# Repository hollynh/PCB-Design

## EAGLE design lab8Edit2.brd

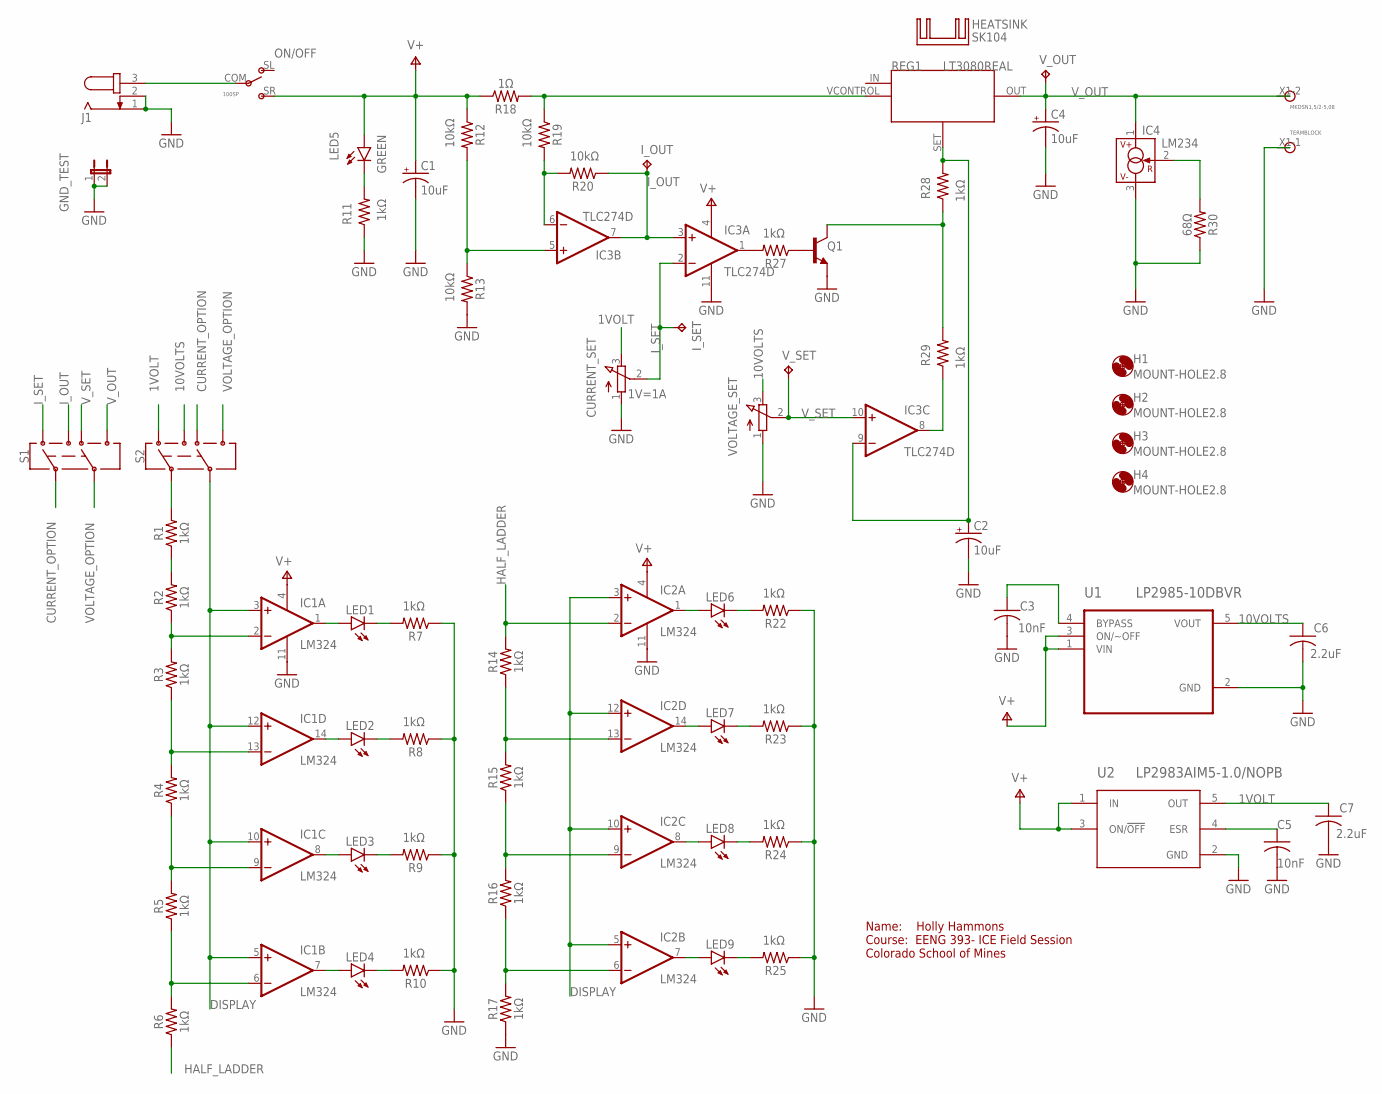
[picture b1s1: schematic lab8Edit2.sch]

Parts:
C1, C2, C4: 10uF; PANASONIC_B
C3, C5: 10nF; C1206
C6, C7: 2.2uF; C1206
CURRENT_SET: 1V=1A; EVUF
GND_TEST: JP1E; JP1
H1, H2, H3, H4: MOUNT-HOLE2.8; 2,8
HEATSINK: SK104
IC1, IC2: LM324; SO14
IC3: TLC274D; SO14
IC4: LM234; TO92
I_OUT: TPPAD1-13; P1-13
I_SET: TPPAD1-13; P1-13
J1: JACK-PLUG0; SPC4077
LED1, LED2, LED3, LED4, LED6, LED7, LED8, LED9: LEDCHIPLED_1206; CHIPLED_1206
LED5: GREEN; CHIPLED_1206
MKDSN1,5/2-5,08: TERMBLOCK
ON/OFF: 100SP; SP100
Q1: TRANS_NPN-MMBTA42; SOT23-3
R1, R2, R3, R4, R5, R6, R7, R8, R9, R10, R11, R14, R15, R16, R17, R22, R23, R24, R25, R27, R28, R29: 1kΩ; R1206
R12, R13, R19, R20: 10kΩ; R1206
R18: 1Ω; 0411/15
R30: 68Ω; R1206
REG1: LT3080REAL
S1, S2: SWITCH-DPDT-SMD-AYZ0202; SWITCH_DPDT_SMD_AYZ0202
U1: LP2985-10DBVR; SOT95P280X145-5N
U2: LP2983AIM5-1.0/NOPB; SOT95P280X145-5N
VOLTAGE_SET: EVUF2A; EVUF
V_OUT: TPPAD1-13; P1-13
V_SET: TPPAD1-13; P1-13

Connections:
1VOLT: C7.1, CURRENT_SET.3 (E), S2.3, U2.5 (OUT)
10VOLTS: C6.1, S2.1, U1.5 (VOUT), VOLTAGE_SET.3 (E)
CURRENT_OPTION: S1.2, S2.6
DISPLAY: IC1.3 (+IN), IC1.5 (+IN), IC1.10 (+IN), IC1.12 (+IN), IC2.3 (+IN), IC2.5 (+IN), IC2.10 (+IN), IC2.12 (+IN), S2.5
GND: C1.-, C2.-, C3.2, C4.-, C5.2, C6.2, C7.2, CURRENT_SET.1 (A), GND_TEST.1, GND_TEST.2, IC1.11 (V-), IC2.11 (V-), IC3.11 (V-), IC4.3 (V-), J1.1, J1.2, MKDSN1,5/2-5,08.X1-1, Q1.2 (E), R7.1, R8.1, R9.1, R10.1, R11.1, R13.2, R17.1, R22.1, R23.1, R24.1, R25.1, R30.1, U1.2 (GND), U2.2 (GND), VOLTAGE_SET.1 (A)
HALF_LADDER: IC2.2 (-IN), R6.1, R14.2
I_OUT: IC3.3 (+IN), IC3.7 (OUT), I_OUT.TP, R20.1, S1.1
I_SET: CURRENT_SET.2 (S), IC3.2 (-IN), I_SET.TP, S1.3
unnamed: J1.3, ON/OFF.COM
unnamed: LED5.C, R11.2
unnamed: C2.+, IC3.9 (-IN), R28.2, REG1.SET
unnamed: R1.2, S2.2
unnamed: IC3.8 (OUT), R29.1
unnamed: Q1.3 (C), R28.1, R29.2
unnamed: Q1.1 (B), R27.1
unnamed: IC3.5 (+IN), R12.2, R13.1
unnamed: IC4.2 (R), R30.2
unnamed: R18.2, R19.1, REG1.VCONTROL (VCTL)
unnamed: IC3.6 (-IN), R19.2, R20.2
unnamed: IC3.1 (OUT), R27.2
unnamed: LED2.C, R8.2
unnamed: IC1.6 (-IN), R5.1, R6.2
unnamed: IC1.9 (-IN), R4.1, R5.2
unnamed: IC1.13 (-IN), R3.1, R4.2
unnamed: IC1.2 (-IN), R2.1, R3.2
unnamed: R1.1, R2.2
unnamed: C3.1, U1.4 (BYPASS)
unnamed: IC1.7 (OUT), LED4.A
unnamed: LED4.C, R10.2
unnamed: IC1.8 (OUT), LED3.A
unnamed: LED3.C, R9.2
unnamed: IC1.14 (OUT), LED2.A
unnamed: IC1.1 (OUT), LED1.A
unnamed: LED1.C, R7.2
unnamed: LED7.C, R23.2
unnamed: IC2.6 (-IN), R16.1, R17.2
unnamed: IC2.9 (-IN), R15.1, R16.2
unnamed: IC2.13 (-IN), R14.1, R15.2
unnamed: C5.1, U2.4 (ESR)
unnamed: IC2.7 (OUT), LED9.A
unnamed: LED9.C, R25.2
unnamed: IC2.8 (OUT), LED8.A
unnamed: LED8.C, R24.2
unnamed: IC2.14 (OUT), LED7.A
unnamed: IC2.1 (OUT), LED6.A
unnamed: LED6.C, R22.2
V+: C1.+, IC1.4 (V+), IC2.4 (V+), IC3.4 (V+), LED5.A, ON/OFF.SR, R12.1, R18.1, U1.1 (VIN), U1.3 (ON/~OFF), U2.1 (IN), U2.3 (ON/!OFF)
VOLTAGE_OPTION: S1.5, S2.4
V_OUT: C4.+, IC4.1 (V+), MKDSN1,5/2-5,08.X1-2, REG1.OUT, S1.4, V_OUT.TP
V_SET: IC3.10 (+IN), S1.6, VOLTAGE_SET.2 (S), V_SET.TP

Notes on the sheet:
Name: Holly Hammons Course: EENG 393- ICE Field Session Colorado School of Mines

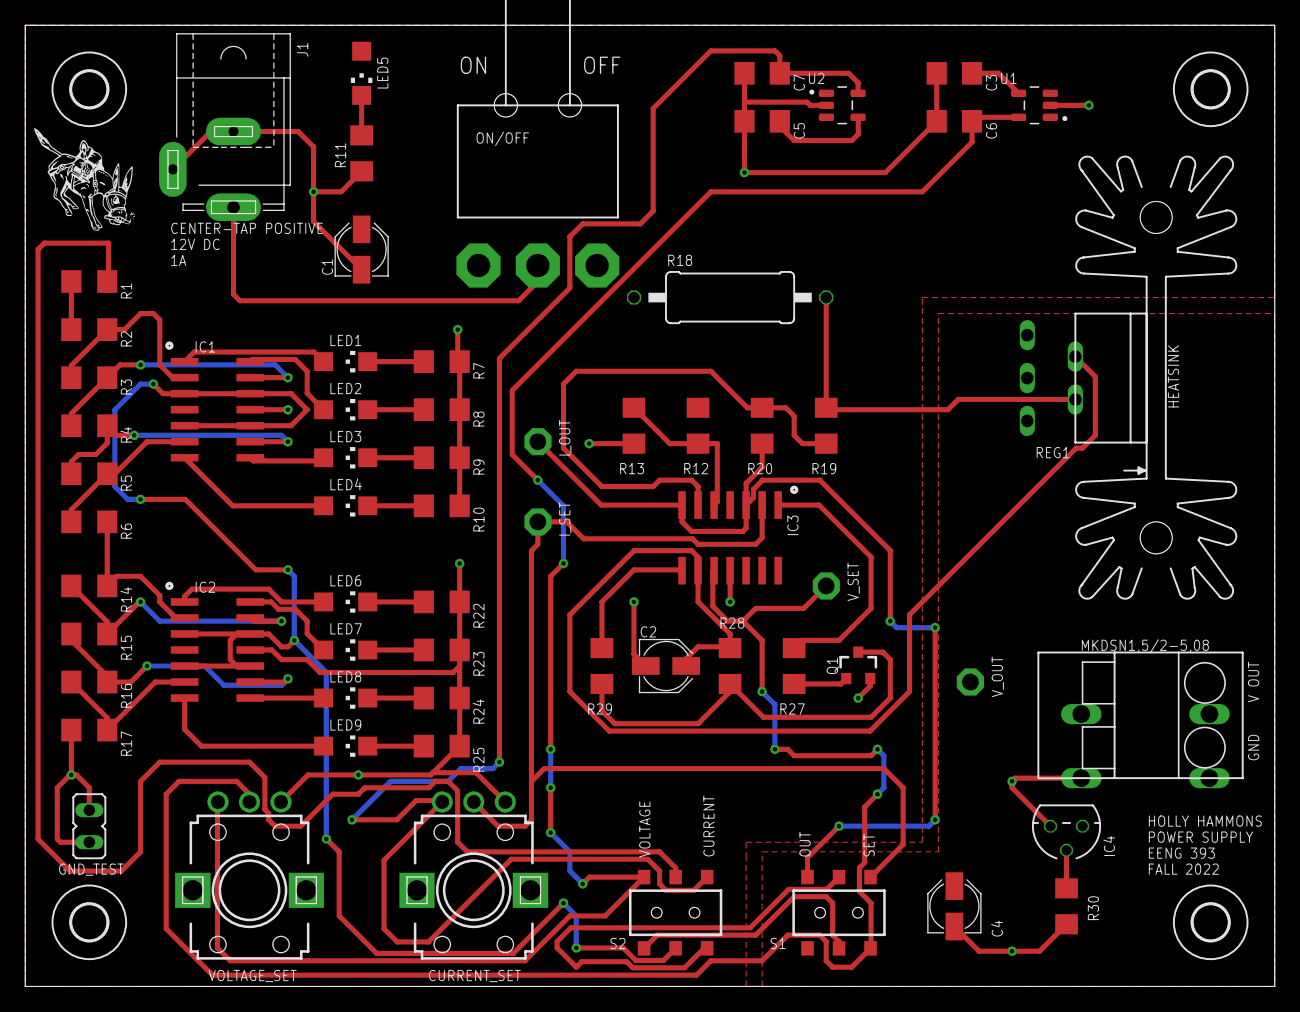
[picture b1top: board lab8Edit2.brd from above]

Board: 2 copper layers, 99.1 x 76.2 mm, 69 parts (0 on the bottom side), 50 nets.

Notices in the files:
parts and their libraries:
SparkFun-DiscreteSemi: Licensing: Creative Commons ShareAlike 4.0 International - https://creativecommons.org/licenses/by-sa/4.0
